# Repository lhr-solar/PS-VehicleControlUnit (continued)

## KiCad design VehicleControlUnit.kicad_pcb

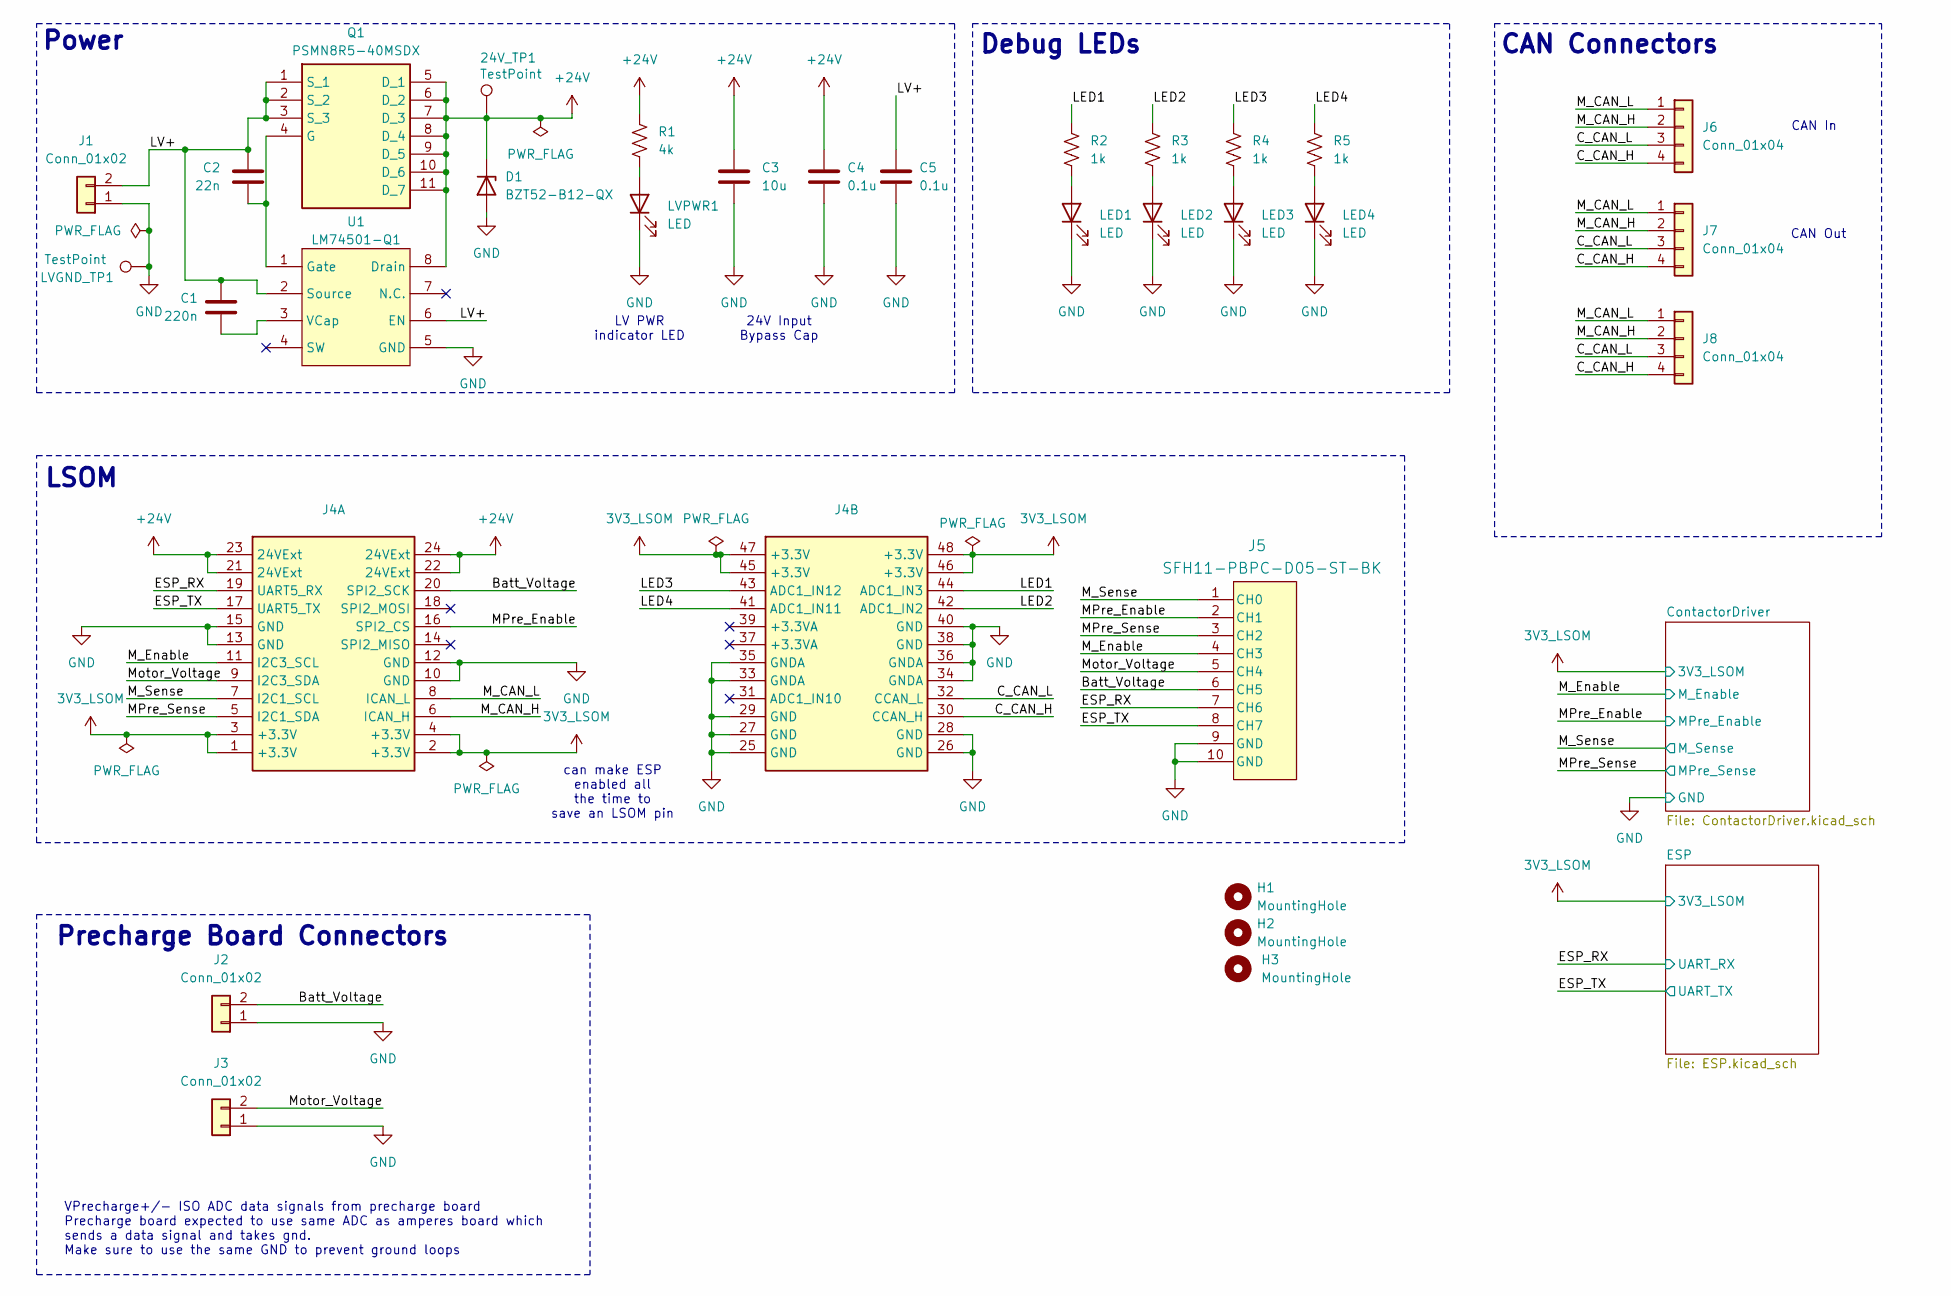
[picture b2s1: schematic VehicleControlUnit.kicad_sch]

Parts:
24V_TP1: TestPoint; TestPoint_HEX_3mmID
C1: 220n; C_0603_1608Metric
C2: 22n; C_0603_1608Metric
C3: 10u; C_0603_1608Metric
C4, C5: 0.1u; C_0603_1608Metric
D1: BZT52-B12-QX; BZT52B12QX
H1, H2, H3: MountingHole; MountingHole_3.2mm_M3
J1, J2, J3: Conn_01x02; Molex_Nano-Fit_105309-xx02_1x02_P2.50mm_Vertical
J4: LeaderSOM
J5: SFH11-PBPC-D05-ST-BK; CONN_SFH11-xxxC-D05-ST-XX_SUL
J6, J7: Conn_01x04; Molex_Nano-Fit_105309-xx04_1x04_P2.50mm_Vertical
J8: Conn_01x04; PinHeader_1x04_P2.54mm_Vertical
LED1, LED2, LED3, LED4: LED; LED_0603_1608Metric
LVGND_TP1: TestPoint; TestPoint_HEX_3mmID
LVPWR1: LED; LED_0603_1608Metric
Q1: PSMN8R5-40MSDX; BUK7M1780EX; Mouser Part Number 771-PSMN8R5-40MSDX
R1: 4k; R_0603_1608Metric
R2, R3, R4, R5: 1k; R_0603_1608Metric
U1: LM74501-Q1; SOT-23-8

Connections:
3V3_LSOM: J4.1 (+3.3V), J4.2 (+3.3V), J4.3 (+3.3V), J4.4 (+3.3V), J4.45 (+3.3V), J4.46 (+3.3V), J4.47 (+3.3V), J4.48 (+3.3V); also elsewhere on the board
+24V: 24V_TP1.1, C3.1, C4.1, D1.1 (K), J4.21 (24VExt), J4.22 (24VExt), J4.23 (24VExt), J4.24 (24VExt), Q1.5 (D_1), Q1.6 (D_2), Q1.7 (D_3), Q1.8 (D_4), Q1.9 (D_5), Q1.10 (D_6), Q1.11 (D_7), R1.1, U1.8 (Drain); also elsewhere on the board
/Batt_Voltage: J2.2, J4.20 (SPI2_SCK), J5.6 (CH5)
/C_CAN_H: J4.30 (CCAN_H), J6.4, J7.4, J8.4
/C_CAN_L: J4.32 (CCAN_L), J6.3, J7.3, J8.3
/ESP_RX: J4.19 (UART5_RX), J5.7 (CH6); also elsewhere on the board
/ESP_TX: J4.17 (UART5_TX), J5.8 (CH7); also elsewhere on the board
/LED1: J4.44 (ADC1_IN3), R2.1
/LED2: J4.42 (ADC1_IN2), R3.1
/LED3: J4.43 (ADC1_IN12), R4.1
/LED4: J4.41 (ADC1_IN11), R5.1
/LV+: C1.2, C2.2, C5.1, J1.2, Q1.1 (S_1), Q1.2 (S_2), Q1.3 (S_3), U1.2 (Source), U1.6 (EN)
/MPre_Enable: J4.16 (SPI2_CS), J5.2 (CH1); also elsewhere on the board
/MPre_Sense: J4.5 (I2C1_SDA), J5.3 (CH2); also elsewhere on the board
/M_CAN_H: J4.6 (ICAN_H), J6.2, J7.2, J8.2
/M_CAN_L: J4.8 (ICAN_L), J6.1, J7.1, J8.1
/M_Enable: J4.11 (I2C3_SCL), J5.4 (CH3); also elsewhere on the board
/M_Sense: J4.7 (I2C1_SCL), J5.1 (CH0); also elsewhere on the board
/Motor_Voltage: J3.2, J4.9 (I2C3_SDA), J5.5 (CH4)
GND: C3.2, C4.2, C5.2, D1.2 (A), J1.1, J2.1, J3.1, J4.10 (GND), J4.12 (GND), J4.13 (GND), J4.15 (GND), J4.25 (GND), J4.26 (GND), J4.27 (GND), J4.28 (GND), J4.29 (GND), J4.33 (GNDA), J4.34 (GNDA), J4.35 (GNDA), J4.36 (GNDA), J4.38 (GND), J4.40 (GND), J5.9 (GND), J5.10 (GND), LED1.1 (K), LED2.1 (K), LED3.1 (K), LED4.1 (K), LVGND_TP1.1, LVPWR1.1 (K), U1.5 (GND); also elsewhere on the board
unnamed: LED1.2 (A), R2.2
unnamed: LED2.2 (A), R3.2
unnamed: LED3.2 (A), R4.2
unnamed: LED4.2 (A), R5.2
unnamed: LVPWR1.2 (A), R1.2
unnamed: C2.1, Q1.4 (G), U1.1 (Gate)
unnamed: C1.1, U1.3 (VCap)

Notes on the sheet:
Precharge Board Connectors
CAN In
can make ESP enabled all the time to save an LSOM pin
Power
24V Input Bypass Cap
VPrecharge+/- ISO ADC data signals from precharge board Precharge board expected to use same ADC as amperes board which sends a data signal and takes gnd. Make sure to use the same GND to prevent ground loops
LV PWR indicator LED
LSOM
Debug LEDs
CAN Out
CAN Connectors

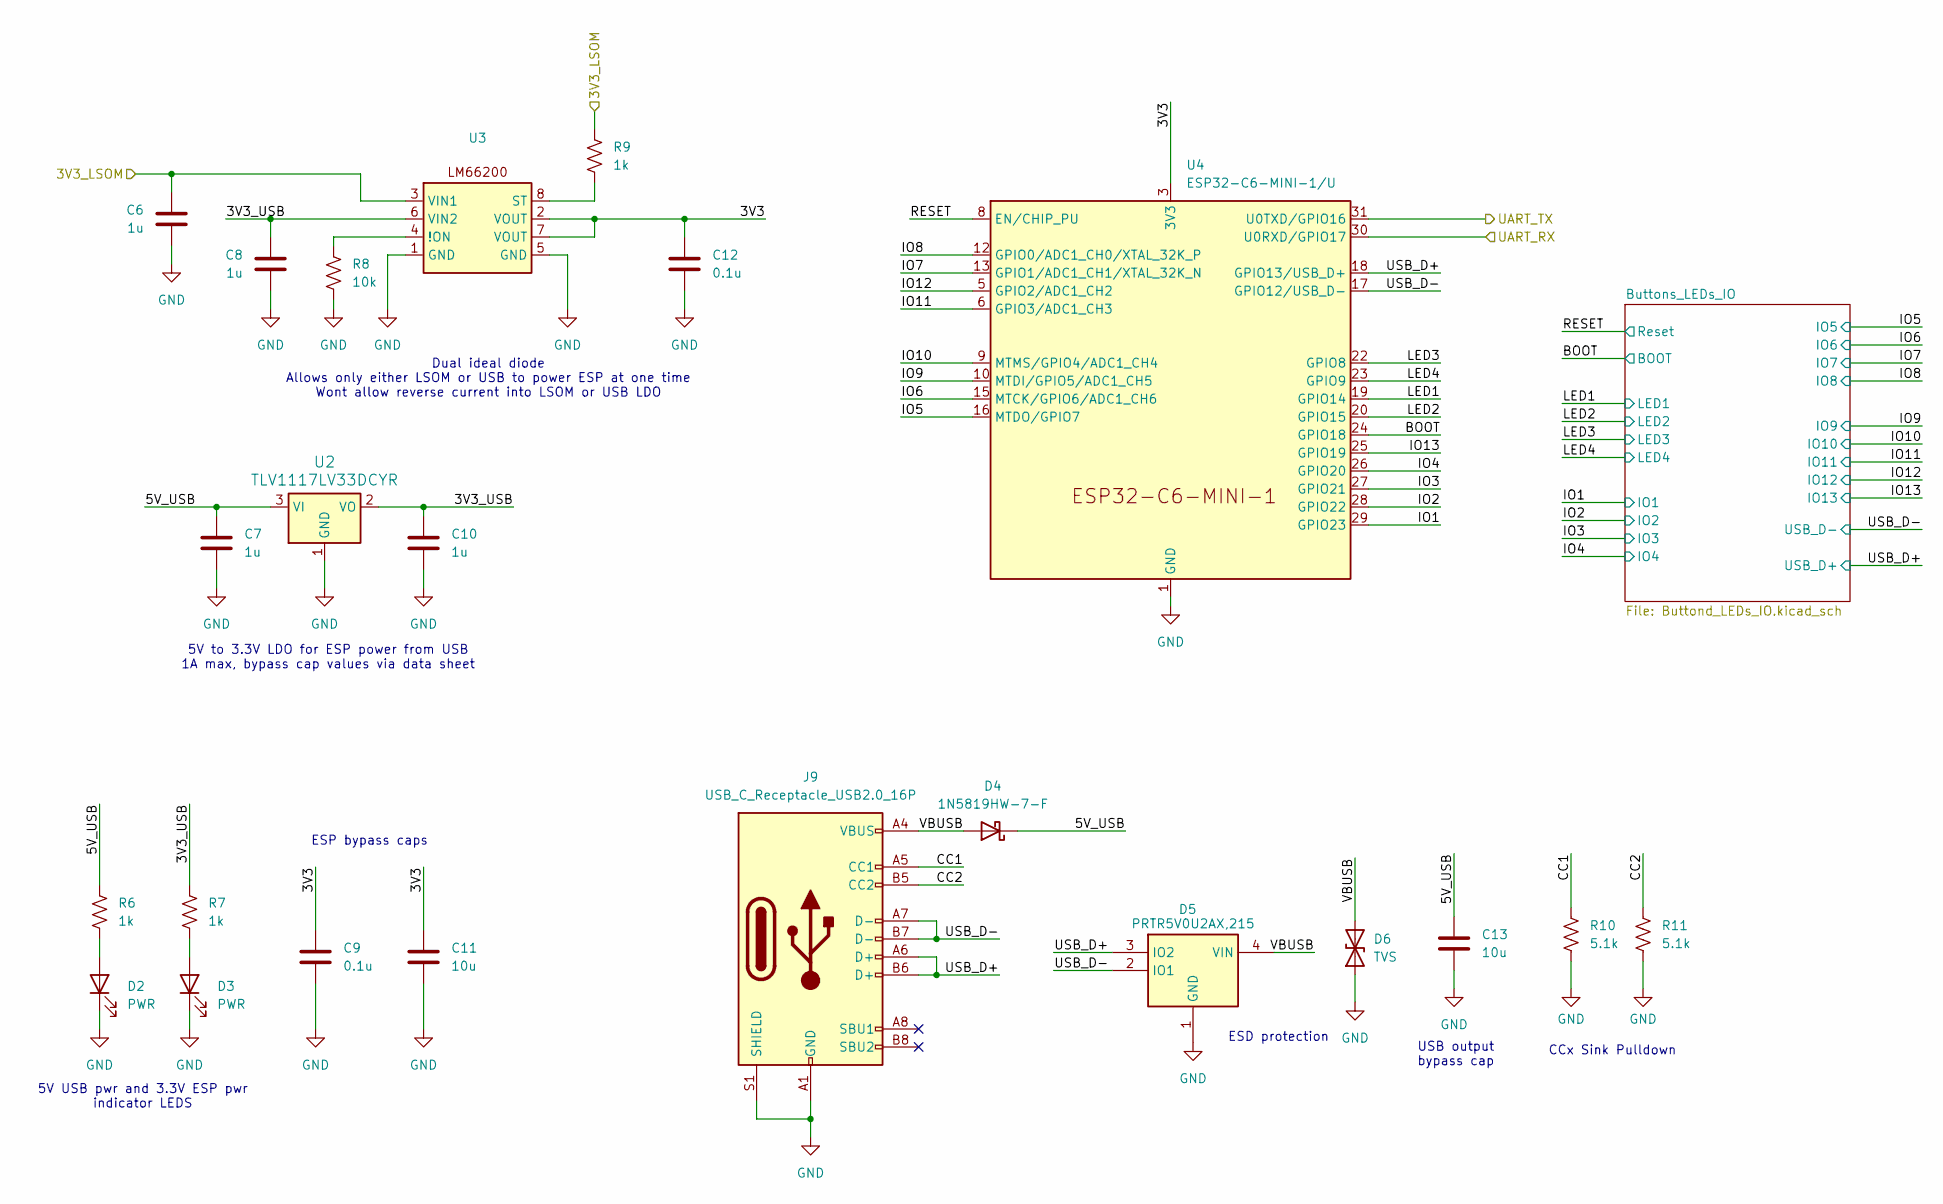
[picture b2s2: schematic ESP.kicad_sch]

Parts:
C6, C7, C8, C10: 1u; C_0603_1608Metric
C9, C12: 0.1u; C_0603_1608Metric
C11, C13: 10u; C_0603_1608Metric
D2, D3: PWR; LED_0603_1608Metric
D4: 1N5819HW-7-F; D_SOD-123
D5: PRTR5V0U2AX,215; PRTR5V0U2X; Mouser Part Number 771-PRTR5V0U2AX-T/R
D6: TVS; D_0603_1608Metric
J9: USB_C_Receptacle_USB2.0_16P; USB_C_Receptacle_GCT_USB4105-xx-A_16P_TopMnt_Horizontal
R6, R7, R9: 1k; R_0603_1608Metric
R8: 10k; R_0603_1608Metric
R10, R11: 5.1k; R_0603_1608Metric
U2: TLV1117LV33DCYR; SOT-223-3_TabPin2
U3: SOTFL50P160X60-8N
U4: ESP32-C6-MINI-1/U; ESP32-C6-MINI-1

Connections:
3V3_LSOM: C6.1, R9.1, U3.3 (VIN1); also elsewhere on the board
/ESP/3V3: C9.1, C11.1, C12.1, U3.2 (VOUT), U3.7 (VOUT), U4.3 (3V3)
/ESP/3V3_USB: C8.1, C10.1, R7.1, U2.2 (VO), U3.6 (VIN2)
/ESP/5V_USB: C7.1, C13.1, D4.1 (K), R6.1, U2.3 (VI)
/ESP/BOOT: U4.24 (GPIO18); also elsewhere on the board
/ESP/CC1: J9.A5 (CC1), R10.1
/ESP/CC2: J9.B5 (CC2), R11.1
/ESP/IO1: U4.29 (GPIO23); also elsewhere on the board
/ESP/IO2: U4.28 (GPIO22); also elsewhere on the board
/ESP/IO3: U4.27 (GPIO21); also elsewhere on the board
/ESP/IO4: U4.26 (GPIO20); also elsewhere on the board
/ESP/IO5: U4.16 (MTDO/GPIO7); also elsewhere on the board
/ESP/IO6: U4.15 (MTCK/GPIO6/ADC1_CH6); also elsewhere on the board
/ESP/IO7: U4.13 (GPIO1/ADC1_CH1/XTAL_32K_N); also elsewhere on the board
/ESP/IO8: U4.12 (GPIO0/ADC1_CH0/XTAL_32K_P); also elsewhere on the board
/ESP/IO9: U4.10 (MTDI/GPIO5/ADC1_CH5); also elsewhere on the board
/ESP/IO10: U4.9 (MTMS/GPIO4/ADC1_CH4); also elsewhere on the board
/ESP/IO11: U4.6 (GPIO3/ADC1_CH3); also elsewhere on the board
/ESP/IO12: U4.5 (GPIO2/ADC1_CH2); also elsewhere on the board
/ESP/IO13: U4.25 (GPIO19); also elsewhere on the board
/ESP/LED1: U4.19 (GPIO14); also elsewhere on the board
/ESP/LED2: U4.20 (GPIO15); also elsewhere on the board
/ESP/LED3: U4.22 (GPIO8); also elsewhere on the board
/ESP/LED4: U4.23 (GPIO9); also elsewhere on the board
/ESP/RESET: U4.8 (EN/CHIP_PU); also elsewhere on the board
/ESP/USB_D+: D5.3 (IO2), J9.A6 (D+), J9.B6 (D+), U4.18 (GPIO13/USB_D+)
/ESP/USB_D-: D5.2 (IO1), J9.A7 (D-), J9.B7 (D-), U4.17 (GPIO12/USB_D-)
/ESP/VBUSB: D4.2 (A), D5.4 (VIN), D6.2 (A2), J9.A4 (VBUS), J9.A9 (VBUS), J9.B4 (VBUS), J9.B9 (VBUS)
/ESP_RX: U4.30 (U0RXD/GPIO17); also elsewhere on the board
/ESP_TX: U4.31 (U0TXD/GPIO16); also elsewhere on the board
GND: C6.2, C7.2, C8.2, C9.2, C10.2, C11.2, C12.2, C13.2, D2.1 (K), D3.1 (K), D5.1 (GND), D6.1 (A1), J9.A1 (GND), J9.A12 (GND), J9.B1 (GND), J9.B12 (GND), J9.S1 (SHIELD), R8.2, R10.2, R11.2, U2.1 (GND), U3.1 (GND), U3.5 (GND), U4.1 (GND), U4.2 (GND), U4.11 (GND), U4.14 (GND), U4.36 (GND), U4.37 (GND), U4.38 (GND), U4.39 (GND), U4.40 (GND), U4.41 (GND), U4.42 (GND), U4.43 (GND), U4.44 (GND), U4.45 (GND), U4.46 (GND), U4.47 (GND), U4.48 (GND), U4.49 (GND), U4.50 (GND), U4.51 (GND), U4.52 (GND), U4.53 (GND); also elsewhere on the board
unnamed: D2.2 (A), R6.2
unnamed: D3.2 (A), R7.2
unnamed: R8.1, U3.4 (!ON)
unnamed: R9.2, U3.8 (ST)

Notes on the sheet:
Dual ideal diode Allows only either LSOM or USB to power ESP at one time Wont allow reverse current into LSOM or USB LDO
5V USB pwr and 3.3V ESP pwr indicator LEDS
USB output bypass cap
ESD protection
CCx Sink Pulldown
ESP bypass caps
5V to 3.3V LDO for ESP power from USB 1A max, bypass cap values via data sheet

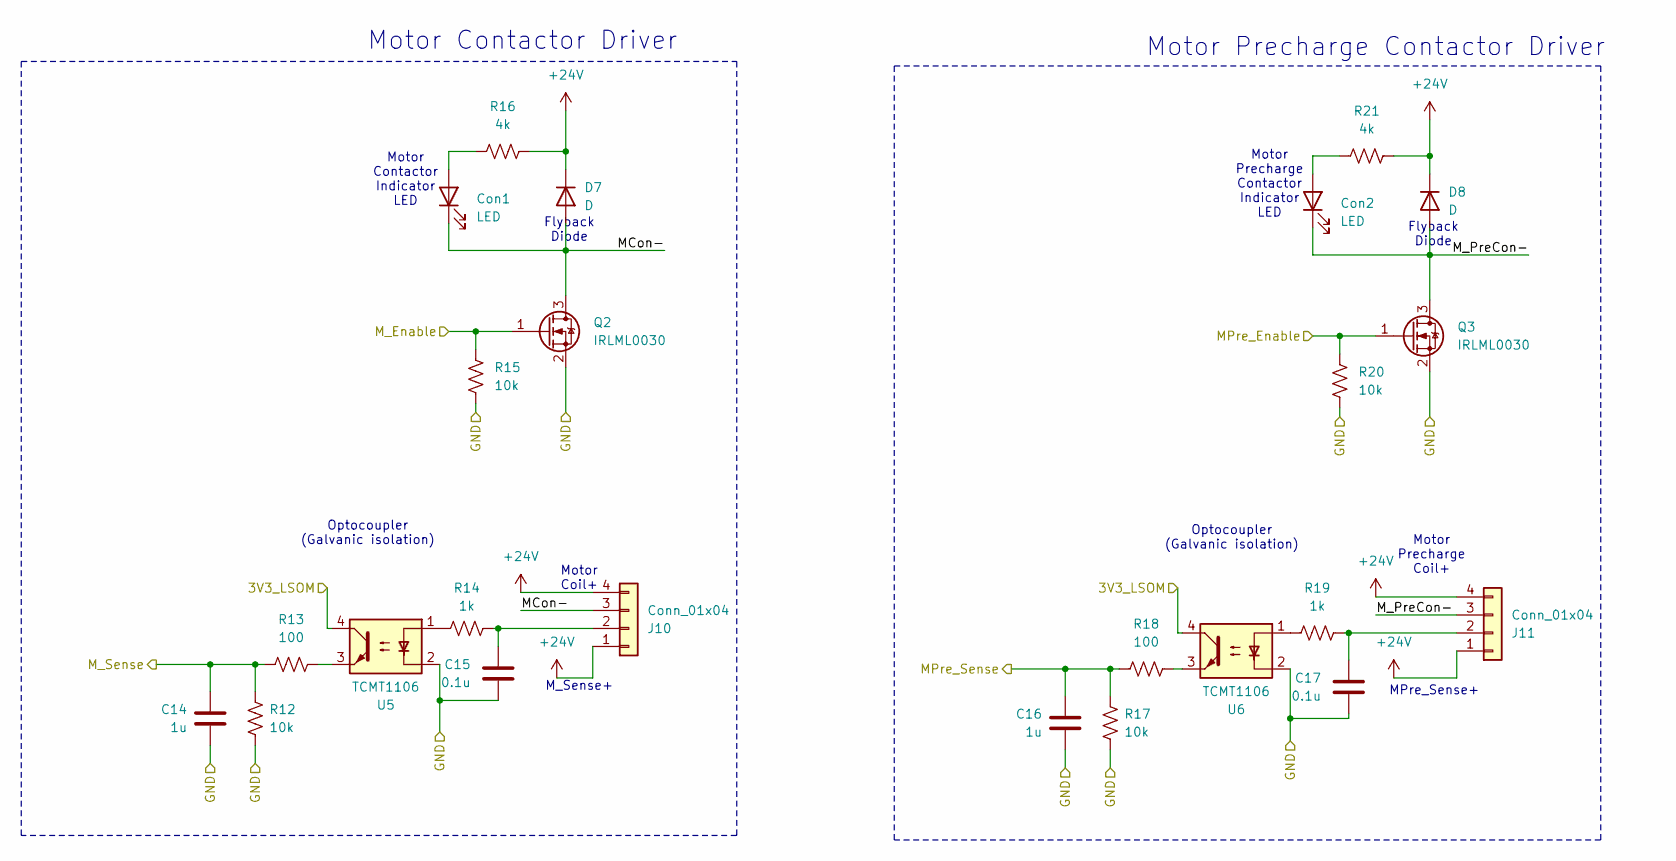
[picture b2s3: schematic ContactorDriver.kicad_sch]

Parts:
C14, C16: 1u; C_0603_1608Metric
C15, C17: 0.1u; C_0603_1608Metric
Con1, Con2: LED; LED_0603_1608Metric
D7, D8: D; SODFL4724X108N
J10, J11: Conn_01x04; Molex_Nano-Fit_105309-xx04_1x04_P2.50mm_Vertical
Q2, Q3: IRLML0030; SOT-23
R12, R15, R17, R20: 10k; R_0603_1608Metric
R13, R18: 100; R_0603_1608Metric
R14, R19: 1k; R_0603_1608Metric
R16, R21: 4k; R_0603_1608Metric
U5, U6: TCMT1106; SOP-4_4.4x2.6mm_P1.27mm

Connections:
3V3_LSOM: U5.4, U6.4; also elsewhere on the board
+24V: D7.1 (K), D8.1 (K), J10.1, J10.4, J11.1, J11.4, R16.2, R21.2; also elsewhere on the board
/ContactorDriver/MCon-: Con1.1 (K), D7.2 (A), J10.3, Q2.3 (D)
/ContactorDriver/M_PreCon-: Con2.1 (K), D8.2 (A), J11.3, Q3.3 (D)
/MPre_Enable: Q3.1 (G), R20.1; also elsewhere on the board
/MPre_Sense: C16.2, R17.1, R18.1; also elsewhere on the board
/M_Enable: Q2.1 (G), R15.1; also elsewhere on the board
/M_Sense: C14.2, R12.1, R13.1; also elsewhere on the board
GND: C14.1, C15.2, C16.1, C17.2, Q2.2 (S), Q3.2 (S), R12.2, R15.2, R17.2, R20.2, U5.2, U6.2; also elsewhere on the board
unnamed: Con1.2 (A), R16.1
unnamed: Con2.2 (A), R21.1
unnamed: C15.1, J10.2, R14.1
unnamed: C17.1, J11.2, R19.1
unnamed: R13.2, U5.3
unnamed: R14.2, U5.1
unnamed: R18.2, U6.3
unnamed: R19.2, U6.1

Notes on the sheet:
Motor Precharge Contactor Driver
Optocoupler (Galvanic isolation)
Motor Precharge Coil+
Motor Contactor Indicator LED
Motor Contactor Driver
Motor Coil+
M_Sense+
Flyback Diode
MPre_Sense+
Motor Precharge Contactor Indicator LED

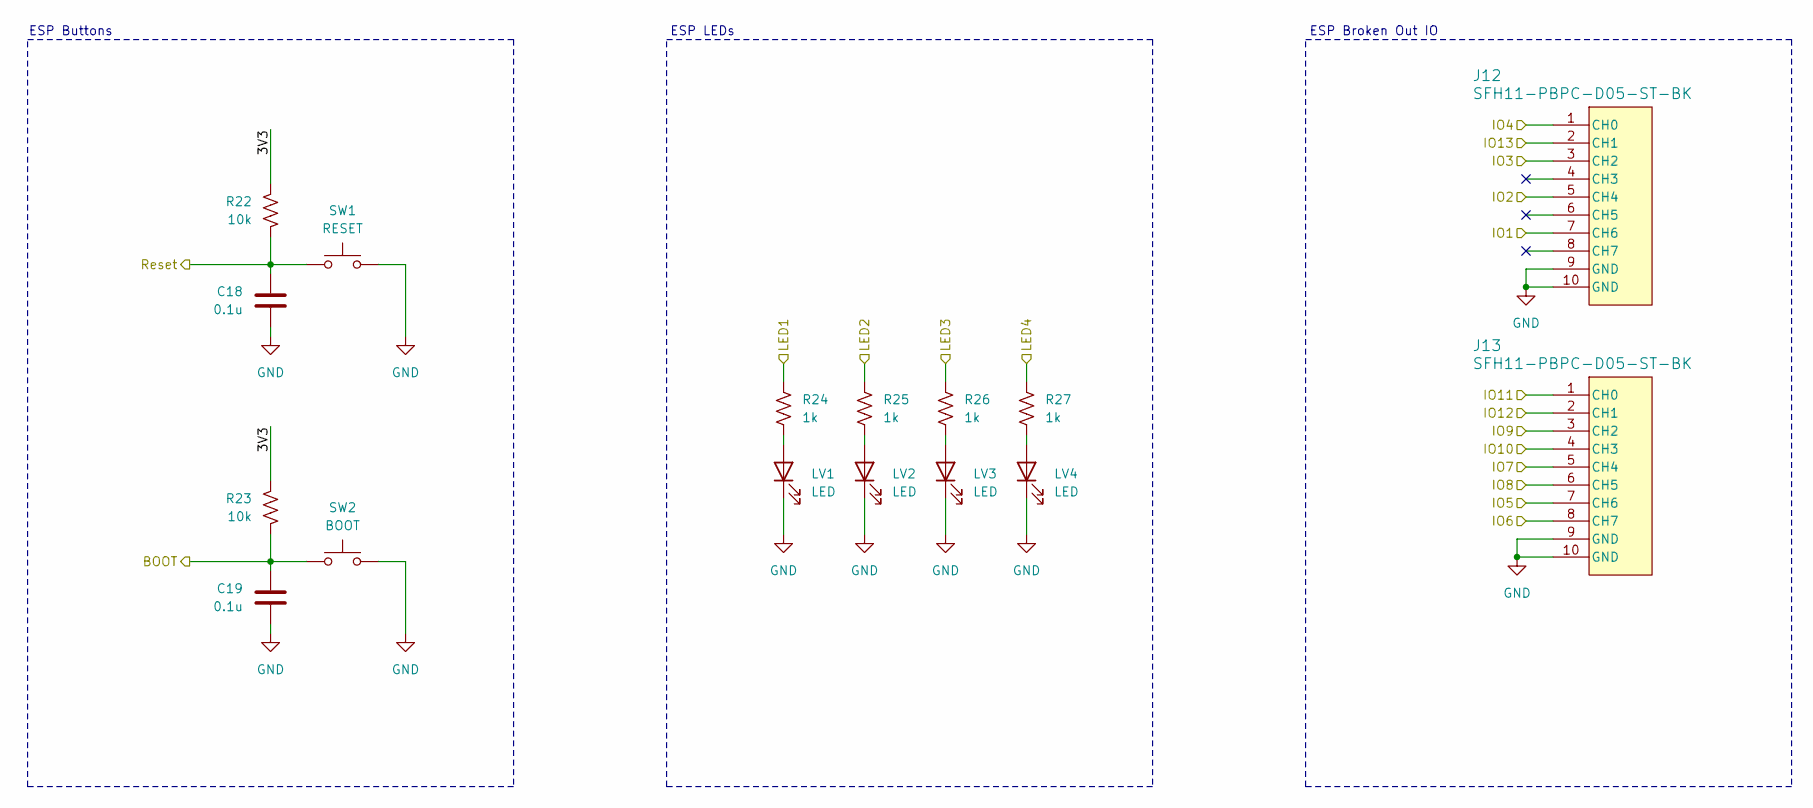
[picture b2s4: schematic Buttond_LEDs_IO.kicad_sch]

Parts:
C18, C19: 0.1u; C_0603_1608Metric
J12, J13: SFH11-PBPC-D05-ST-BK; CONN_SFH11-xxxC-D05-ST-XX_SUL
LV1, LV2, LV3, LV4: LED; LED_0603_1608Metric
R22, R23: 10k; R_0603_1608Metric
R24, R25, R26, R27: 1k; R_0603_1608Metric
SW1: RESET; SW_SPST_B3SL-1002P
SW2: BOOT; SW_SPST_B3SL-1002P

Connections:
/ESP/BOOT: C19.1, R23.2, SW2.3 (B), SW2.4 (B); also elsewhere on the board
/ESP/Buttons_LEDs_IO/3V3: R22.1, R23.1
/ESP/IO1: J12.7 (CH6); also elsewhere on the board
/ESP/IO2: J12.5 (CH4); also elsewhere on the board
/ESP/IO3: J12.3 (CH2); also elsewhere on the board
/ESP/IO4: J12.1 (CH0); also elsewhere on the board
/ESP/IO5: J13.7 (CH6); also elsewhere on the board
/ESP/IO6: J13.8 (CH7); also elsewhere on the board
/ESP/IO7: J13.5 (CH4); also elsewhere on the board
/ESP/IO8: J13.6 (CH5); also elsewhere on the board
/ESP/IO9: J13.3 (CH2); also elsewhere on the board
/ESP/IO10: J13.4 (CH3); also elsewhere on the board
/ESP/IO11: J13.1 (CH0); also elsewhere on the board
/ESP/IO12: J13.2 (CH1); also elsewhere on the board
/ESP/IO13: J12.2 (CH1); also elsewhere on the board
/ESP/LED1: R24.1; also elsewhere on the board
/ESP/LED2: R25.1; also elsewhere on the board
/ESP/LED3: R26.1; also elsewhere on the board
/ESP/LED4: R27.1; also elsewhere on the board
/ESP/RESET: C18.1, R22.2, SW1.3 (B), SW1.4 (B); also elsewhere on the board
GND: C18.2, C19.2, J12.9 (GND), J12.10 (GND), J13.9 (GND), J13.10 (GND), LV1.1 (K), LV2.1 (K), LV3.1 (K), LV4.1 (K), SW1.1 (A), SW1.2 (A), SW2.1 (A), SW2.2 (A); also elsewhere on the board
unnamed: LV1.2 (A), R24.2
unnamed: LV2.2 (A), R25.2
unnamed: LV3.2 (A), R26.2
unnamed: LV4.2 (A), R27.2

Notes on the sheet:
ESP Broken Out IO
ESP Buttons
ESP LEDs

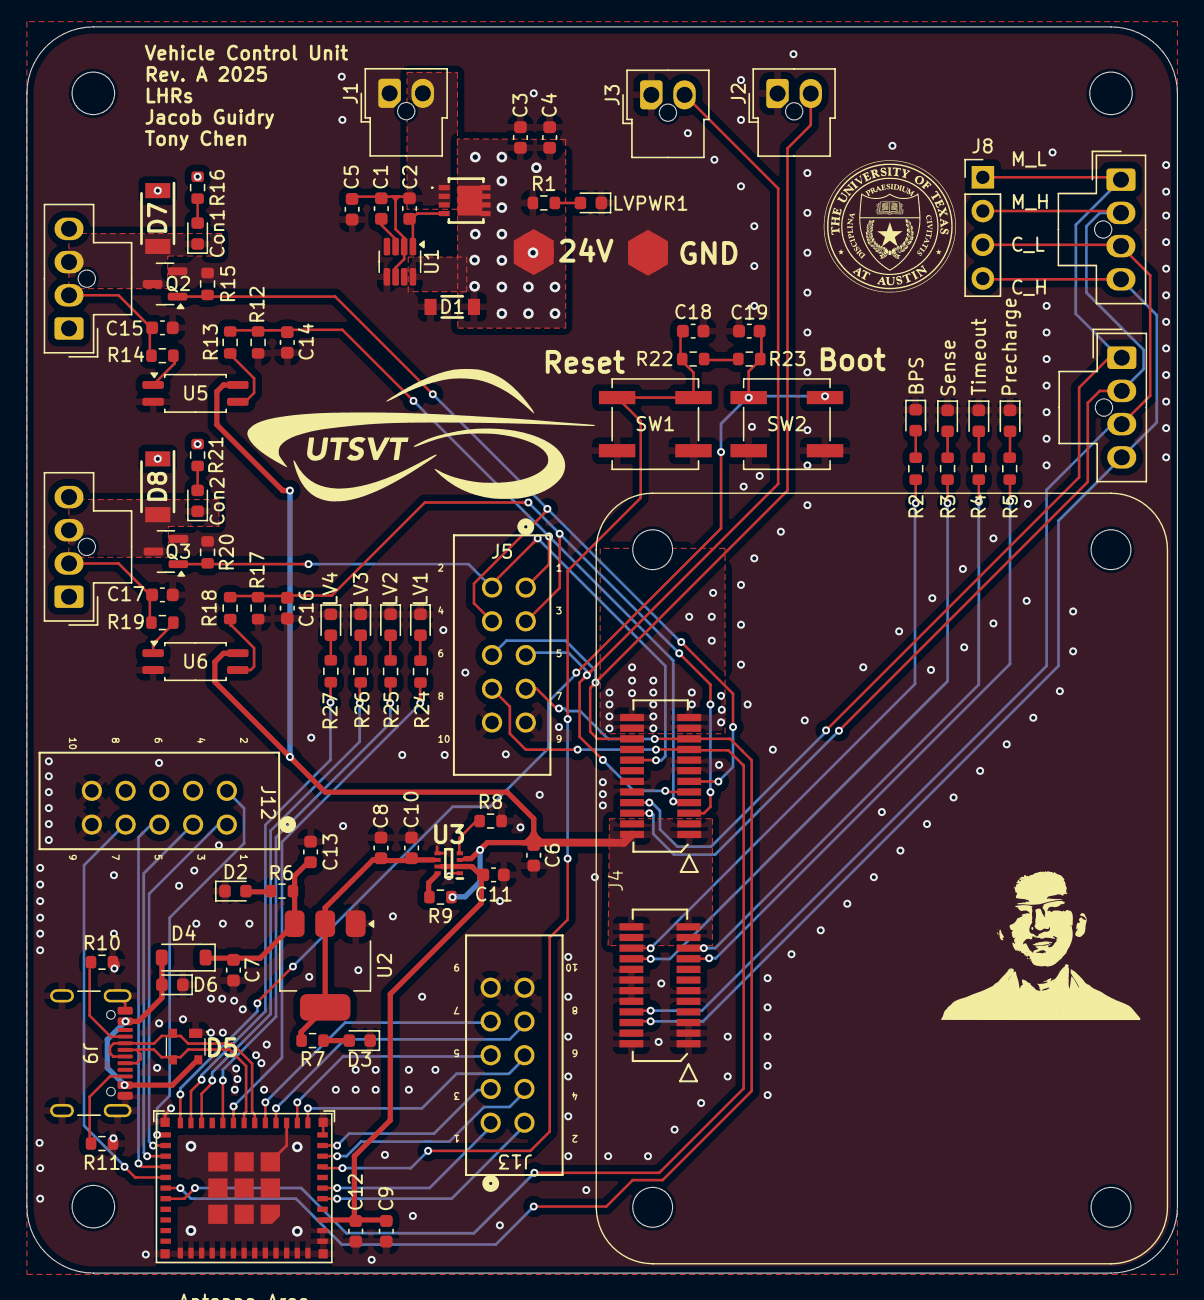
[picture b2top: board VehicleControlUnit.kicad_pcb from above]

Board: 2 copper layers, 86.6 x 93.8 mm, 94 parts (0 on the bottom side), 73 nets.

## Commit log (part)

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2025-04-01 blank VCU sch
2025-04-03 inital sch
2025-04-07 sch additions
2025-04-14 alsdkjf
2025-04-17 sch for review missing LSOM
2025-04-22 add lsom sym
2025-04-22 review LSOM
2025-04-25 review sch one last time
2025-05-18 added opto's to sense signals
2025-05-24 first revision
2025-05-28 tweaking
2025-05-31 review changes
2025-06-15 is it time to give up :3
2025-06-16 minor fixes
2025-07-25 moving to kicad-bild
2025-07-26 fuck the rats nest im doing it tomorrow
2025-07-26 routing done
2025-07-28 lakshay nitpicks
2025-08-09 shrunk the board by 7mm
2025-08-10 replaced 0805 with 0603, changed logic analyzer symbol and silkscreen
2025-08-12 embedding 3d models
2025-08-21 added image to schematic
2025-08-24 as;ldfkjasdl;f
2025-08-24 maybe final revA revision
2025-08-24 small zener diode change
2025-08-26 ravi's bs
2025-08-26 bom stuff
2025-08-26 more bom stuff
2025-09-02 start of RevB. BOM for revA
2025-09-05 renamed RevB to RevA-Firmware
2025-09-06 software setup
2025-09-06 starting to copy active precharge code
2025-09-12 RevA (#1)
    * blank VCU sch
    * fix
    * inital sch
    * sch additions
    * initial commit post VCU block diagram
    * alsdkjf
2025-10-11 rpp oopsie
2025-10-11 kms rpp
2025-10-11 alsdjflasjfsad
2025-10-21 ESP fucked
2025-10-27 fucked up esp
2025-11-01 fixing submodules part 2
2025-11-03 workday
2025-11-06 fixed schematic
2025-11-24 rev B
2025-11-24 stitching vias
2025-12-01 333T presentation
2025-12-18 organize into two folders
2025-12-18 updated lsom model
2025-12-18 grrr
2025-12-18 weirdo wants me to fix stuff that wasn't my fault completely
2025-12-18 removed duplicates
2025-12-18 removed duplicate jlc
2025-12-19 removed part numbers
2025-12-22 review council
2025-12-24 more vias
2025-12-24 bunch a haters
2025-12-29 fixing
2026-01-04 i hate everything about you - three days grace
2026-01-05 added connector models
2026-01-06 scuffed stuff
2026-01-06 jlcpcb files
2026-01-07 added mosfets
2026-01-13 compiling code
2026-01-13 change name of tests
2026-01-13 add instructions
2026-01-13 spell exclusing correctly
2026-01-13 add workflow
2026-01-13 move workflow to correct folder
2026-01-13 fix embedded-sharepoint submodule
2026-01-13 womp womp
2026-01-13 prepare urself ravi
2026-01-13 tony doesn't understand how directories work
2026-01-14 bah 2
2026-01-15 .vscode dir creation handling
2026-01-19 Made RTOS Tasks, fault arch, small CAN changes,
2026-01-24 First few bits of firmware, copy pasted the ADC and clock stuff and wrote the read function and outlined precharge logic
2026-01-28 Removed an infinite loop
2026-01-29 fix build actions cript
2026-01-29 Fix build action (#6)
    * fix build actions cript
    * add production test file
2026-01-31 split motor and telem tasks
2026-01-31 Created driver folders and moved stuff out of main, rewrote to use fixed point instead of floating
2026-02-01 closer to compiling
2026-02-01 All comments addressed, plus wrote h files for the new stuff I created
2026-02-06 Everything except VCU pins and contactor stuff has been done, the test is prob some garbage, how makefile so i can build and fix errors
2026-02-08 fixed some build issues
2026-02-08 fixed pins
2026-02-16 might need to run on board to compile for CAN
2026-02-17 refactored everything so that it compiles
2026-02-17 update embedded sharepoint
2026-02-20 working adc init
2026-02-21 fixed fwd/rev logic and gonna delete runtime FSM
2026-02-21 added braking, this feels more and more cursed
2026-02-22 ADC task creation, working on fixing it though
2026-02-24 Half functional ADC reading (spits out ADC values that are like half of what they should be/ 3.3V = ~1990)
2026-02-24 ADC fixed
2026-02-25 printf worky
2026-02-25 contactors working
2026-02-26 generate CAN from DBC
2026-02-26 correct linking for can gen
2026-02-26 Added real can msgs and init task
2026-02-26 Added some semaphores/mutexes and fixed some deps
2026-02-26 made the CAN recv literals
2026-02-26 some shit
2026-02-27 Added workflows and some changes
2026-02-27 Github workflows
2026-02-28 Created a fault handler task to run at a higher priority than precharge task
2026-02-28 Code compiles now and added a fix for build error relating to husart3
2026-02-28 Fixed typo in main.c
2026-03-02 Working FaultHandler task, a few faults remain to be added
2026-03-02 Laksee safetee approved (ts works), fault handler works, need to add functionality to set precharge state bits for moco code use later on
2026-03-03 sending moco can
2026-03-03 random bullshit go!
2026-03-03 FaultHandler cleaned up
2026-03-03 motor telemetry task + add newlines at the end
2026-03-03 Includes have been cleaned up and tasks have been moved to main
2026-03-03 BRUH
2026-03-03 add motor power command
2026-03-03 LEDs now work properly with main, TODO: Implement switch case led set and phase out old shit
2026-03-03 motor safe bits
2026-03-03 some testing stuff
2026-03-03 add prohelion can docs
2026-03-04 Added LUTs and removed the math operations for ADC
2026-03-04 Separated functions into other drivers from inits
2026-03-04 please ishdeshpa save me D:
2026-03-04 add init task include to other task files
2026-03-04 holy fuck, macOS is stupid
2026-03-04 motor spin!
2026-03-04 Canbus Driver (#7)
    * balls
    * balls
    * balls
    * random bullshit go!
    * motor telemetry task + add newlines at the end
    * balls 3
2026-03-04 change to can fd branch
2026-03-04 fixing merges
2026-03-05 Precharge and MotorCAN drivers (#5)
    * First few bits of firmware, copy pasted the ADC and clock stuff and wrote the read function and outlined precharge logic
    * Created driver folders and moved stuff out of main, rewrote to use fixed point instead of floating
    * All comments addressed, plus wrote h files for the new stuff I created
    * Everything except VCU pins and contactor stuff has been done, the test is prob some garbage, how makefile so i can build and fix errors
    * comments addressed plus led blinking code
    * fixed some build issues
2026-03-05 not building but errors are stupid, will fix tn
2026-03-06 it compilin 🍆😋
2026-03-07 reorganize UART init and add ESP32 init
2026-03-07 added adc read to esp32_test
2026-03-07 sends but doubled
2026-03-07 integrated motor telemetry and control in main
2026-03-07 partial printing
2026-03-08 moved can logic out of fsm and made a drivers folder
2026-03-08 fix some shit?
2026-03-08 working but bad
2026-03-08 submod
2026-03-08 fixed some fsm stuff
2026-03-09 fix build for motor controller test
2026-03-09 made a bunch of changes and now nothing work :(
2026-03-09 skeletonizing code to restart
2026-03-10 add defines for stack size
2026-03-10 prat brought back chungus
2026-03-10 add fault string struct
2026-03-11 valid gemini comments
2026-03-11 Precharge + Motor Control Integration (#10)
    * balls
    * integrated motor telemetry and control in main
    * balls
    * balls
    * gem en eye
    * fix build for motor controller test
2026-03-11 storing for now before lakshay breaks my code
2026-03-11 tony (gavin) chen
2026-03-11 dumba
2026-03-11 ESP32 Drivers (#9)
    * started shell driver
    * balls
    * reorganize UART init and add ESP32 init
    * balls
    * balls
    * balls
2026-03-11 whatever
2026-03-12 starting revC
2026-03-18 hehehehehe
2026-03-18 gem an eye
2026-03-20 fixed canbus test, rewrote faults
2026-03-24 started on multiple addresses
2026-03-24 360C lecture
2026-03-24 addd to init task
2026-03-25 fixed arduino compile errors
2026-03-28 Testing sending CAN messages for precharge voltages and VCU status should be ready. I changed FaultBits so that precharge states are now in a new enum state_bit_t. According changes have been made to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
2026-03-28 saving before changing branches
2026-03-29 Caught one setFaultBit call that hadn't been changed to setStateBit. Precharge sequence now works again. Moving on to CAN.
2026-04-03 Made tests for CAN
2026-04-03 Build work frfr
2026-04-04 Implemented so called schizo CAN test
2026-04-05 CAN still does not work
2026-04-05 shifting stuff around
2026-04-05 Renamed some shit that didnt have matching names or smth
2026-04-08 lowkenuinely jumpinng off the pickle roof
2026-04-09 changed carcan stuff to motor can change back
2026-04-09 testing some stuff
2026-04-09 less goonery
2026-04-10 working can send
2026-04-10 working on can receive
2026-04-10 Please work fuck as shit
2026-04-10 CAN functionality successfully integrated with Precharge task. Properly waits on Motor Igntion and sends CAN messages out for Status and Voltages. Made a dummy task (DriverInputTask) which repeatedly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
2026-04-10 Created a Check Ignition State function, compares saved state and what is received over CAN. If CAN = 1 and Saved = 0, move from ignition to precharge. If CAN = 0 and Saved = 1, start the ignition of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
2026-04-10 Created outlines for receiving BPS faults and subsequently opening contactors. Function for shutdown/opening contactors is outlined but i still need to move the code and add the calls for all of the 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
2026-04-11 added release flatten workflow, let's see if it works
2026-04-11 rename
2026-04-11 switched back car to motor
2026-04-11 for consistency, use same env var in both steps
2026-04-11 Fixing build issues
2026-04-11 Build issue fix
2026-04-11 Fix build issues post merge
2026-04-11 More build fixes
2026-04-11 Build hopefully works
2026-04-11 precharge integration (#13)
    * Testing sending CAN messages for precharge voltages and VCU status should be ready. I changed FaultBits so that precharge states are now in a new enum state_bit_t. According changes have been made 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
    * Added the CarCAN messages file, forgot the first time
    * Caught one setFaultBit call that hadn't been changed to setStateBit. Precharge sequence now works again. Moving on to CAN.
    * Made tests for CAN
    * Fix build
    * Build work frfr
2026-04-12 ts shit builds
2026-04-12 precharge working; tested
2026-04-14 erm dawgs -> no dawgs
2026-04-15 stuff semi working
2026-04-15 forwarding works
2026-04-16 kabooom
2026-04-16 itll work trust
2026-04-21 mirror send drive on carcan
2026-04-22 fix oopsie
2026-04-22 add deadzone
2026-04-25 stole code
2026-04-26 Update submodule to branch_name
2026-04-26 testing stuff
2026-04-30 add release artifact workflow
2026-05-02 updated new smaller NMOS
2026-05-02 fix current limiters (rollover + swoc)
2026-05-03 initial
2026-05-03 some changes
2026-06-01 parthiv shit??
2026-06-07 some debug
2026-06-07 fixed printf
2026-06-12 some print statements
2026-06-19 debugging
2026-06-26 fsm_monkey_integration: working motor control + dumb ROM bootloader
    Port the working motor control from fsm_bootload onto the clean fsm_integration
    base (Embedded-Sharepoint stays on main; no resident ESBLT bootloader):
    - Fix the SWOC/rollover current limiter (commit f2c8257). The old
    apply_swoc_speed_limit() returned a uint8_t percent (0-100) that was fmin'd
    against a 0.0-1.0 current fraction, so the speed cap never applied and the VCU
    streamed full requested current -> the Wavesculptor tripped its software
2026-06-26 fsm_monkey: use Embedded-Sharepoint bootloader_lite (bl-lite)
    Move the lite ROM-bootloader logic out of the VCU and into the shared submodule
    (branch bl-lite). The VCU now just opts in:
    - main(): bootloader_lite_init() routes faults to the ROM bootloader.
    - DumbBootloaderTask: thin USART3 listener -> bootloader_lite_feed_byte(), replies
    BOOTACK, then bootloader_lite_enter_rom(). (RAM-vector/backup-register code removed
    from the VCU; it lives in the submodule now.)
2026-06-26 bump Embedded-Sharepoint bl-lite (bootloader_lite docs on docs site)
2026-06-26 bump Embedded-Sharepoint bl-lite (bootloader_lite header doc)
2026-06-26 gitignore: ignore nested .vscode dirs (*/.vscode)
2026-06-26 fsm_monkey: opt into bootloader_lite via macros in main
    Replace the explicit init calls with the macro opt-in: main.c defines
    USE_BOOTLOADER + BOOTLOADER_ON_HARDFAULT and calls BOOTLOADER_LITE_SETUP(husart3);
    the listener-task call is dropped from InitTask. Submodule bumped to bl-lite f65362a.
    Verified with `nix develop` (links stm32g473xx.elf).
2026-06-26 Update submodule to latest desired-branch
2026-06-26 fix tests + update bootloader implementation
